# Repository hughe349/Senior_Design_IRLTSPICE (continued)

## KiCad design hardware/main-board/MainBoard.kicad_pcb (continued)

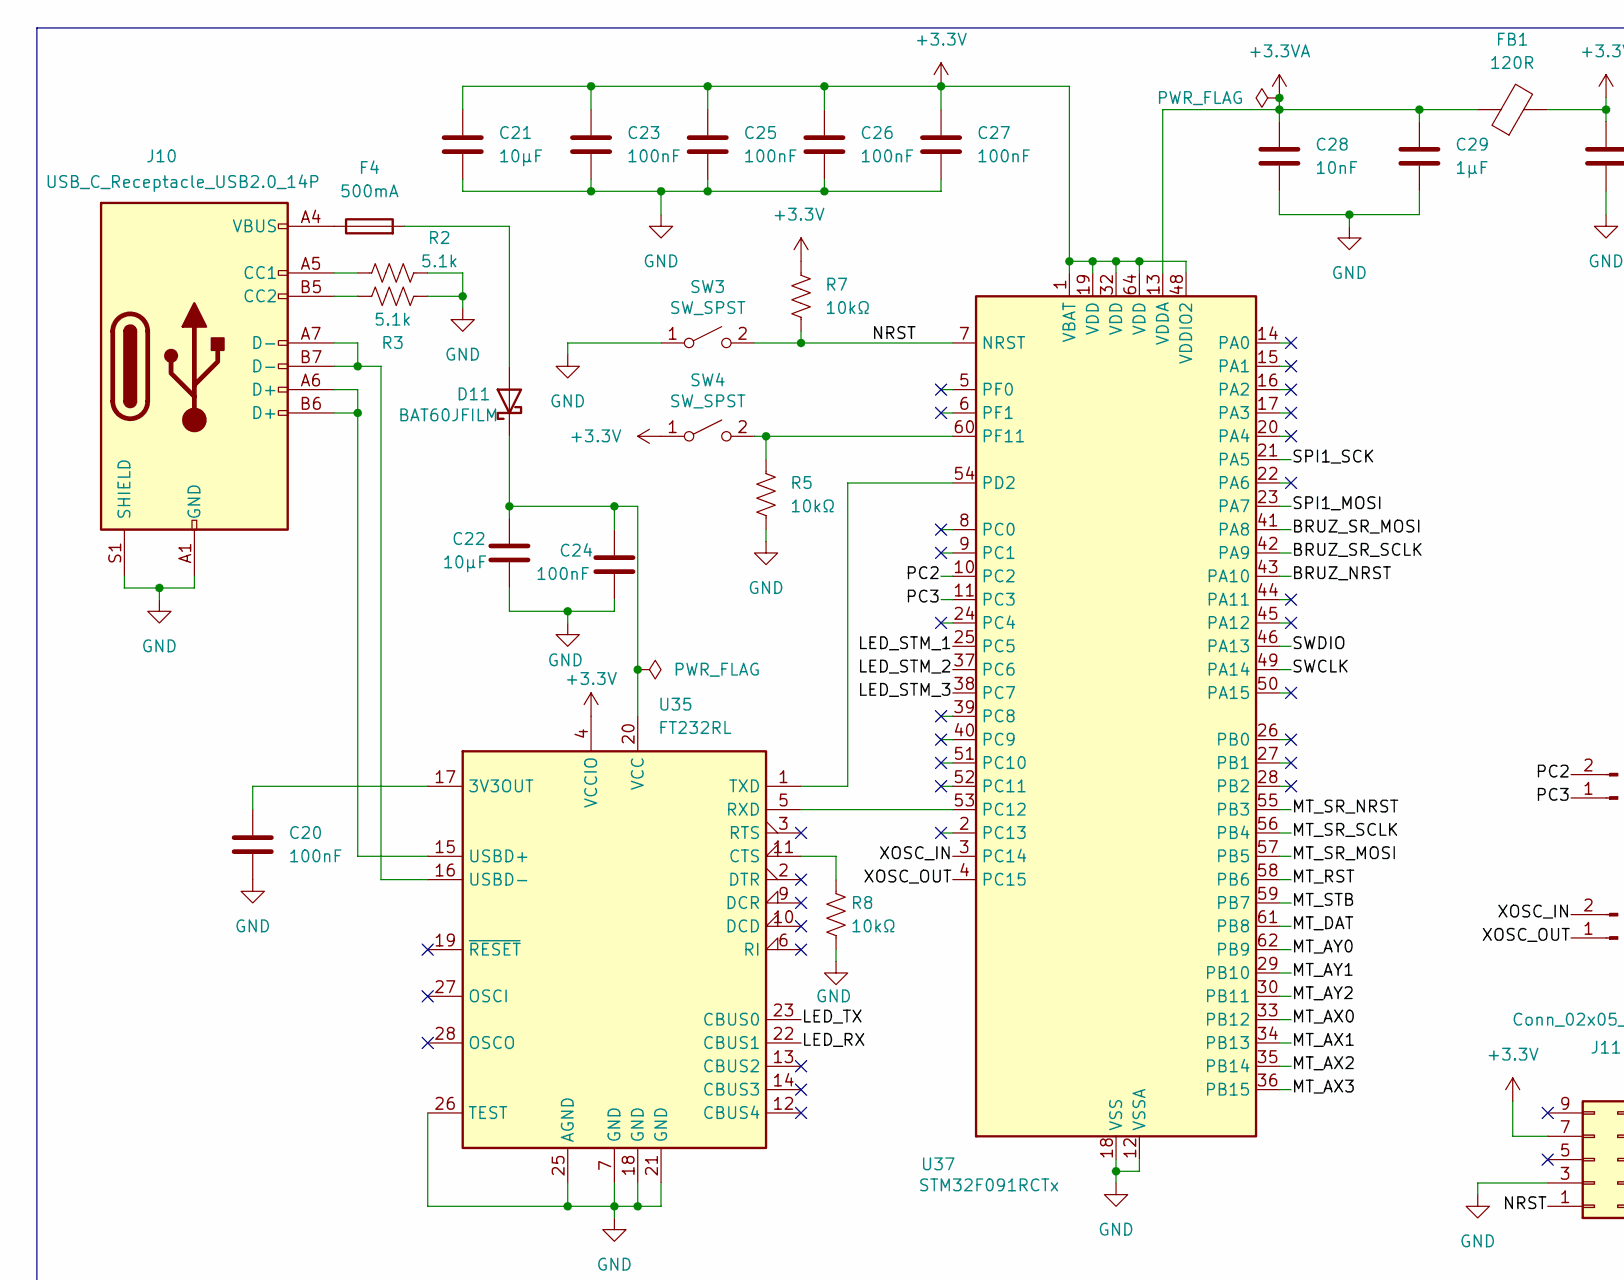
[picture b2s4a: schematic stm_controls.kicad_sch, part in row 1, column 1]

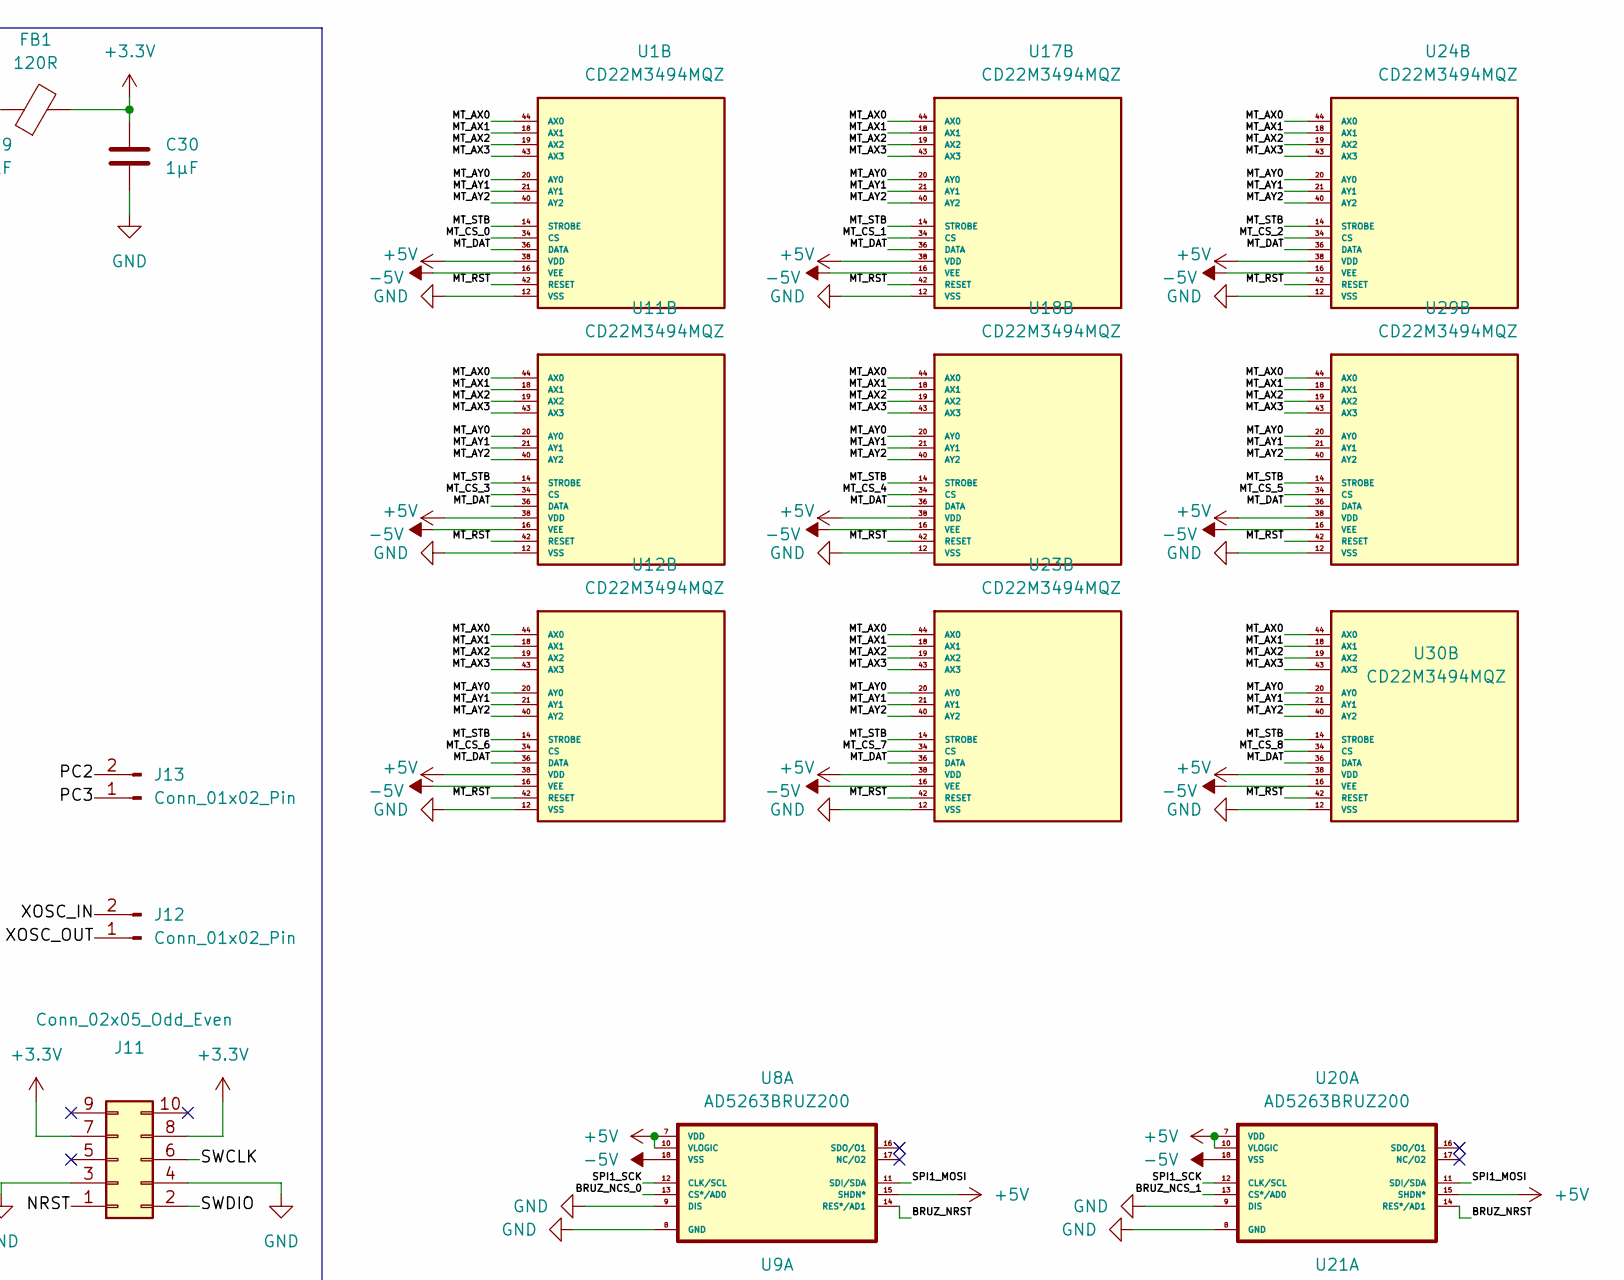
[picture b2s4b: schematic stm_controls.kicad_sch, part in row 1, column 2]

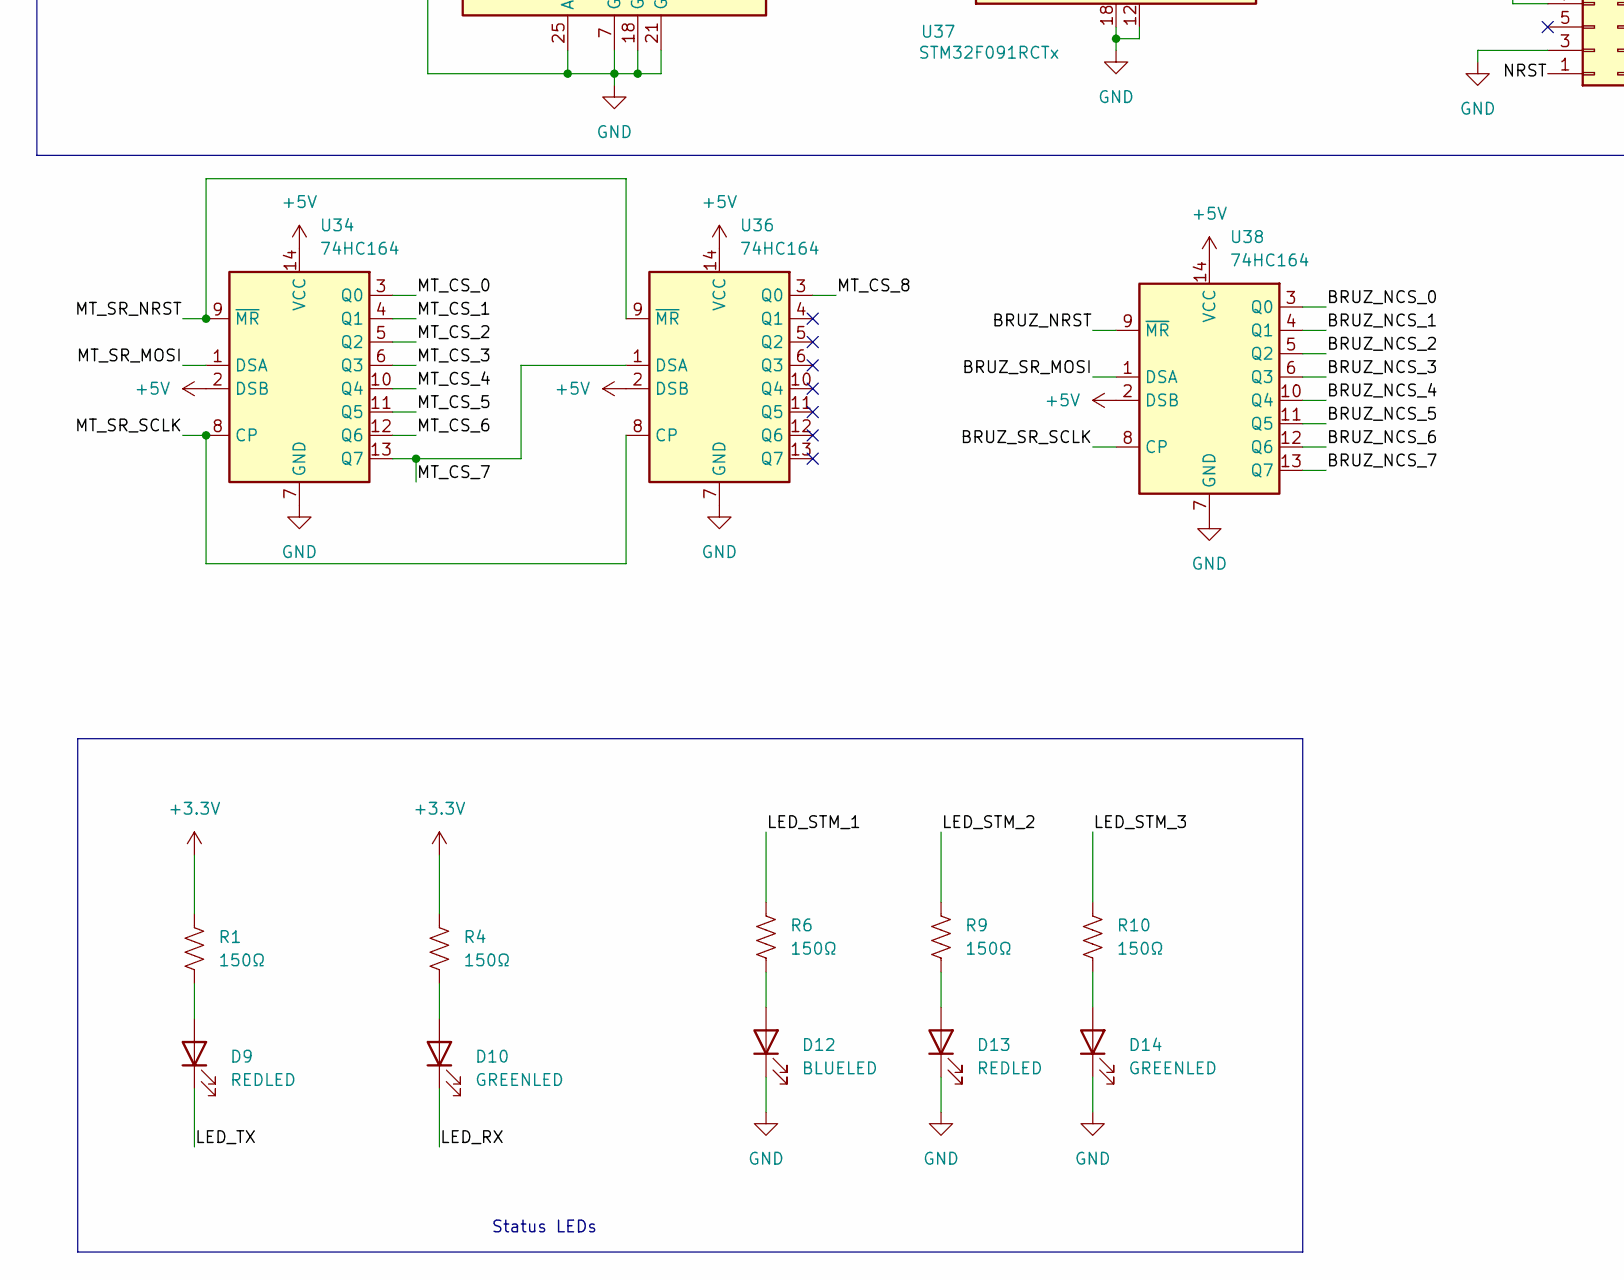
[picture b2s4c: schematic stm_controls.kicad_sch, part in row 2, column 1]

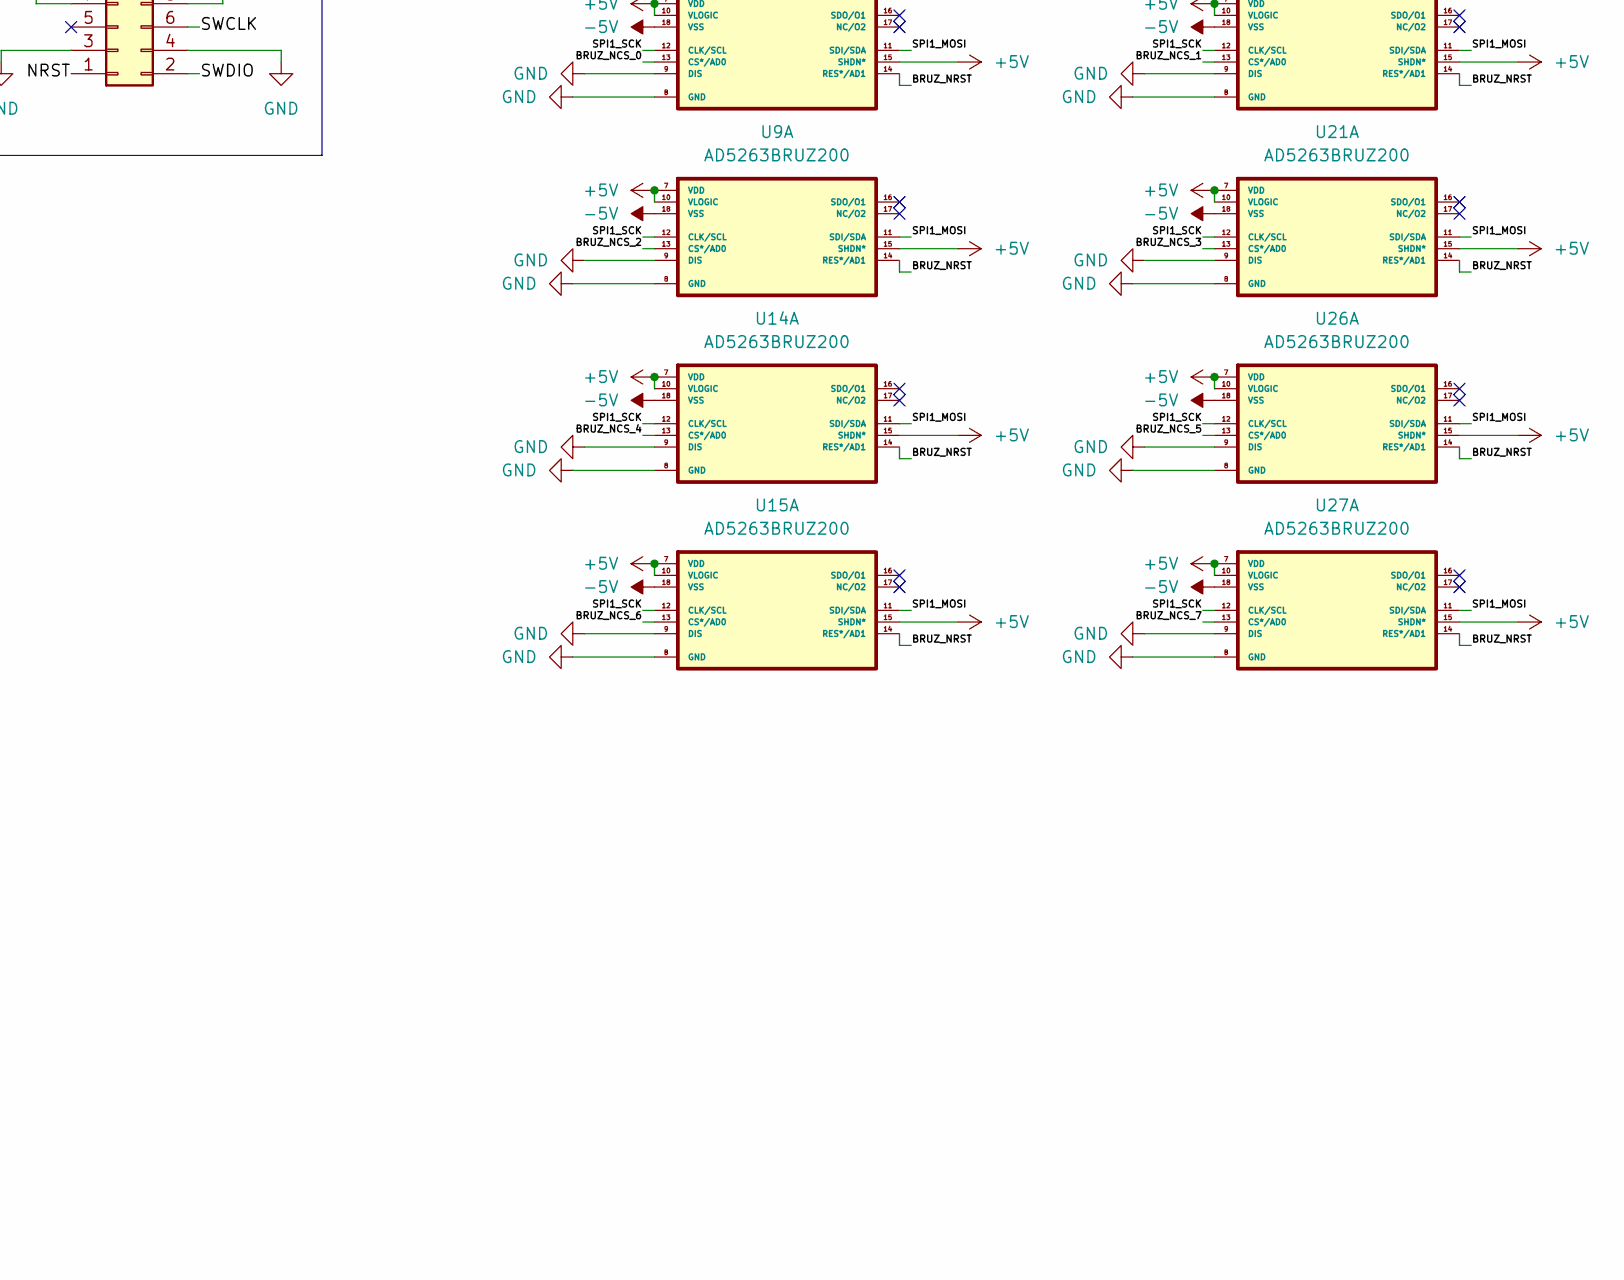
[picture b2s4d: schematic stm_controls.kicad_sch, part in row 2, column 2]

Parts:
C20, C23, C24, C25, C26, C27: 100nF; C_0603_1608Metric_Pad1.08x0.95mm_HandSolder
C21, C22: 10µF; C_0603_1608Metric_Pad1.08x0.95mm_HandSolder
C28: 10nF; C_0603_1608Metric_Pad1.08x0.95mm_HandSolder
C29, C30: 1µF; C_0603_1608Metric_Pad1.08x0.95mm_HandSolder
D9, D13: REDLED; D_0805_2012Metric_Pad1.15x1.40mm_HandSolder
D10, D14: GREENLED; D_0805_2012Metric_Pad1.15x1.40mm_HandSolder
D11: BAT60JFILM; D_SOD-323_HandSoldering
D12: BLUELED; D_0805_2012Metric_Pad1.15x1.40mm_HandSolder
F4: 500mA; Fuse_0603_1608Metric_Pad1.05x0.95mm_HandSolder
FB1: 120R; L_0603_1608Metric_Pad1.05x0.95mm_HandSolder
J10: USB_C_Receptacle_USB2.0_14P; USB_C_Receptacle_G-Switch_GT-USB-7010ASV
J11: Conn_02x05_Odd_Even; PinHeader_2x05_P2.54mm_Vertical
J12, J13: Conn_01x02_Pin; PinSocket_1x02_P2.54mm_Vertical
R1, R4, R6, R9, R10: 150Ω; R_0603_1608Metric_Pad0.98x0.95mm_HandSolder
R2, R3: 5.1k; R_0603_1608Metric_Pad0.98x0.95mm_HandSolder
R5, R7, R8: 10kΩ; R_0603_1608Metric_Pad0.98x0.95mm_HandSolder
SW3, SW4: SW_SPST; SW_SPST_SKQG_WithoutStem
U1, U11, U12, U17, U18, U23, U24, U29, U30: CD22M3494MQZ; PLCC44_16P66X16P66_INR-M; PARTREV September 2011
U8, U9, U14, U15, U20, U21, U26, U27: AD5263BRUZ200; SOP65P640X120-24N
U34, U36, U38: 74HC164; SOIC-14_3.9x8.7mm_P1.27mm
U35: FT232RL; SSOP-28_5.3x10.2mm_P0.65mm
U37: STM32F091RCTx; LQFP-64_10x10mm_P0.5mm

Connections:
+3.3V: C21.1, C23.1, C25.1, C26.1, C27.1, C30.1, FB1.2, J11.7, J11.8, R1.1, R4.1, R7.1, SW4.1 (A), U35.4 (VCCIO), U37.1 (VBAT), U37.19 (VDD), U37.32 (VDD), U37.48 (VDDIO2), U37.64 (VDD); also elsewhere on the board
+3.3VA: C28.1, C29.1, FB1.1, U37.13 (VDDA)
+5V: U1.38 (VDD), U8.7 (VDD), U8.10 (VLOGIC), U8.15 (SHDN*), U9.7 (VDD), U9.10 (VLOGIC), U9.15 (SHDN*), U11.38 (VDD), U12.38 (VDD), U14.7 (VDD), U14.10 (VLOGIC), U14.15 (SHDN*), U15.7 (VDD), U15.10 (VLOGIC), U15.15 (SHDN*), U17.38 (VDD), U18.38 (VDD), U20.7 (VDD), U20.10 (VLOGIC), U20.15 (SHDN*), U21.7 (VDD), U21.10 (VLOGIC), U21.15 (SHDN*), U23.38 (VDD), U24.38 (VDD), U26.7 (VDD), U26.10 (VLOGIC), U26.15 (SHDN*), U27.7 (VDD), U27.10 (VLOGIC), U27.15 (SHDN*), U29.38 (VDD), U30.38 (VDD), U34.2 (DSB), U34.14 (VCC), U36.2 (DSB), U36.14 (VCC), U38.2 (DSB), U38.14 (VCC); also elsewhere on the board
-5V: U1.16 (VEE), U8.18 (VSS), U9.18 (VSS), U11.16 (VEE), U12.16 (VEE), U14.18 (VSS), U15.18 (VSS), U17.16 (VEE), U18.16 (VEE), U20.18 (VSS), U21.18 (VSS), U23.16 (VEE), U24.16 (VEE), U26.18 (VSS), U27.18 (VSS), U29.16 (VEE), U30.16 (VEE); also elsewhere on the board
/Cell_1_Buff: U1.13 (Y6); also elsewhere on the board
/Cell_1_Out: U18.10 (Y7); also elsewhere on the board
/Cell_2_Buff: U1.10 (Y7); also elsewhere on the board
/MicroController/BRUZ_NCS_0: U8.13 (CS*/AD0), U38.3 (Q0)
/MicroController/BRUZ_NCS_1: U20.13 (CS*/AD0), U38.4 (Q1)
/MicroController/BRUZ_NCS_2: U9.13 (CS*/AD0), U38.5 (Q2)
/MicroController/BRUZ_NCS_3: U21.13 (CS*/AD0), U38.6 (Q3)
/MicroController/BRUZ_NCS_4: U14.13 (CS*/AD0), U38.10 (Q4)
/MicroController/BRUZ_NCS_5: U26.13 (CS*/AD0), U38.11 (Q5)
/MicroController/BRUZ_NCS_6: U15.13 (CS*/AD0), U38.12 (Q6)
/MicroController/BRUZ_NCS_7: U27.13 (CS*/AD0), U38.13 (Q7)
/MicroController/BRUZ_NRST: U8.14 (RES*/AD1), U9.14 (RES*/AD1), U14.14 (RES*/AD1), U15.14 (RES*/AD1), U20.14 (RES*/AD1), U21.14 (RES*/AD1), U26.14 (RES*/AD1), U27.14 (RES*/AD1), U37.43 (PA10), U38.9 (~MR)
/MicroController/BRUZ_SR_MOSI: U37.41 (PA8), U38.1 (DSA)
/MicroController/BRUZ_SR_SCLK: U37.42 (PA9), U38.8 (CP)
/MicroController/LED_RX: D10.1 (K), U35.22 (CBUS1)
/MicroController/LED_STM_1: R6.1, U37.25 (PC5)
/MicroController/LED_STM_2: R9.1, U37.37 (PC6)
/MicroController/LED_STM_3: R10.1, U37.38 (PC7)
/MicroController/LED_TX: D9.1 (K), U35.23 (CBUS0)
/MicroController/MT_AX0: U1.44 (AX0), U11.44 (AX0), U12.44 (AX0), U17.44 (AX0), U18.44 (AX0), U23.44 (AX0), U24.44 (AX0), U29.44 (AX0), U30.44 (AX0), U37.33 (PB12)
/MicroController/MT_AX1: U1.18 (AX1), U11.18 (AX1), U12.18 (AX1), U17.18 (AX1), U18.18 (AX1), U23.18 (AX1), U24.18 (AX1), U29.18 (AX1), U30.18 (AX1), U37.34 (PB13)
/MicroController/MT_AX2: U1.19 (AX2), U11.19 (AX2), U12.19 (AX2), U17.19 (AX2), U18.19 (AX2), U23.19 (AX2), U24.19 (AX2), U29.19 (AX2), U30.19 (AX2), U37.35 (PB14)
/MicroController/MT_AX3: U1.43 (AX3), U11.43 (AX3), U12.43 (AX3), U17.43 (AX3), U18.43 (AX3), U23.43 (AX3), U24.43 (AX3), U29.43 (AX3), U30.43 (AX3), U37.36 (PB15)
/MicroController/MT_AY0: U1.20 (AY0), U11.20 (AY0), U12.20 (AY0), U17.20 (AY0), U18.20 (AY0), U23.20 (AY0), U24.20 (AY0), U29.20 (AY0), U30.20 (AY0), U37.62 (PB9)
/MicroController/MT_AY1: U1.21 (AY1), U11.21 (AY1), U12.21 (AY1), U17.21 (AY1), U18.21 (AY1), U23.21 (AY1), U24.21 (AY1), U29.21 (AY1), U30.21 (AY1), U37.29 (PB10)
/MicroController/MT_AY2: U1.40 (AY2), U11.40 (AY2), U12.40 (AY2), U17.40 (AY2), U18.40 (AY2), U23.40 (AY2), U24.40 (AY2), U29.40 (AY2), U30.40 (AY2), U37.30 (PB11)
/MicroController/MT_CS_0: U1.34 (CS), U34.3 (Q0)
/MicroController/MT_CS_1: U17.34 (CS), U34.4 (Q1)
/MicroController/MT_CS_2: U24.34 (CS), U34.5 (Q2)
/MicroController/MT_CS_3: U11.34 (CS), U34.6 (Q3)
/MicroController/MT_CS_4: U18.34 (CS), U34.10 (Q4)
/MicroController/MT_CS_5: U29.34 (CS), U34.11 (Q5)
/MicroController/MT_CS_6: U12.34 (CS), U34.12 (Q6)
/MicroController/MT_CS_7: U23.34 (CS), U34.13 (Q7), U36.1 (DSA)
/MicroController/MT_CS_8: U30.34 (CS), U36.3 (Q0)
/MicroController/MT_DAT: U1.36 (DATA), U11.36 (DATA), U12.36 (DATA), U17.36 (DATA), U18.36 (DATA), U23.36 (DATA), U24.36 (DATA), U29.36 (DATA), U30.36 (DATA), U37.61 (PB8)
/MicroController/MT_RST: U1.42 (RESET), U11.42 (RESET), U12.42 (RESET), U17.42 (RESET), U18.42 (RESET), U23.42 (RESET), U24.42 (RESET), U29.42 (RESET), U30.42 (RESET), U37.58 (PB6)
/MicroController/MT_SR_MOSI: U34.1 (DSA), U37.57 (PB5)
/MicroController/MT_SR_NRST: U34.9 (~MR), U36.9 (~MR), U37.55 (PB3)
/MicroController/MT_SR_SCLK: U34.8 (CP), U36.8 (CP), U37.56 (PB4)
/MicroController/MT_STB: U1.14 (STROBE), U11.14 (STROBE), U12.14 (STROBE), U17.14 (STROBE), U18.14 (STROBE), U23.14 (STROBE), U24.14 (STROBE), U29.14 (STROBE), U30.14 (STROBE), U37.59 (PB7)
/MicroController/NRST: J11.1, R7.2, SW3.2 (B), U37.7 (NRST)
/MicroController/PC2: J13.2, U37.10 (PC2)
/MicroController/PC3: J13.1, U37.11 (PC3)
/MicroController/SPI1_MOSI: U8.11 (SDI/SDA), U9.11 (SDI/SDA), U14.11 (SDI/SDA), U15.11 (SDI/SDA), U20.11 (SDI/SDA), U21.11 (SDI/SDA), U26.11 (SDI/SDA), U27.11 (SDI/SDA), U37.23 (PA7)
/MicroController/SPI1_SCK: U8.12 (CLK/SCL), U9.12 (CLK/SCL), U14.12 (CLK/SCL), U15.12 (CLK/SCL), U20.12 (CLK/SCL), U21.12 (CLK/SCL), U26.12 (CLK/SCL), U27.12 (CLK/SCL), U37.21 (PA5)
/MicroController/SWCLK: J11.6, U37.49 (PA14)
/MicroController/SWDIO: J11.2, U37.46 (PA13)
/MicroController/XOSC_IN: J12.2, U37.3 (PC14)
/MicroController/XOSC_OUT: J12.1, U37.4 (PC15)
/STD1/C3_in: U17.8 (X10); also elsewhere on the board
/STD1/C3_out: U17.9 (X11); also elsewhere on the board
/STD1/C4_out: U17.7 (X9); also elsewhere on the board
/STD1/R2_out: U18.7 (X9); also elsewhere on the board
/STD1/R4_in: U18.8 (X10); also elsewhere on the board
/STD1/R4_out: U18.9 (X11); also elsewhere on the board
/STD1/Y5: U17.15 (Y5); also elsewhere on the board
/STD1/Y6: U17.13 (Y6); also elsewhere on the board
/STD1/Y7: U17.10 (Y7); also elsewhere on the board
/STD1_Y0: U18.17 (Y4); also elsewhere on the board
/STD1_Y1: U18.15 (Y5); also elsewhere on the board
/STD1_Y2: U18.13 (Y6); also elsewhere on the board
/STD2_Y0: U1.2 (X14); also elsewhere on the board
/STD2_Y1: U1.3 (X15); also elsewhere on the board
/STD2_Y2: U1.4 (X6); also elsewhere on the board
/STD3/Y0: U1.5 (X7); also elsewhere on the board
/STD3/Y1: U1.6 (X8); also elsewhere on the board
/STD3/Y2: U1.7 (X9); also elsewhere on the board
/STD_Out: U1.8 (X10); also elsewhere on the board
GND: C20.2, C21.2, C22.2, C23.2, C24.2, C25.2, C26.2, C27.2, C28.2, C29.2, C30.2, D12.1 (K), D13.1 (K), D14.1 (K), J10.A1 (GND), J10.A12 (GND), J10.B1 (GND), J10.B12 (GND), J10.S1 (SHIELD), J11.3, J11.4, R2.2, R3.2, R5.2, R8.2, SW3.1 (A), U1.12 (VSS), U8.8 (GND), U8.9 (DIS), U9.8 (GND), U9.9 (DIS), U11.12 (VSS), U12.12 (VSS), U14.8 (GND), U14.9 (DIS), U15.8 (GND), U15.9 (DIS), U17.12 (VSS), U17.17 (Y4), U18.12 (VSS), U20.8 (GND), U20.9 (DIS), U21.8 (GND), U21.9 (DIS), U23.12 (VSS), U24.12 (VSS), U26.8 (GND), U26.9 (DIS), U27.8 (GND), U27.9 (DIS), U29.12 (VSS), U30.12 (VSS), U34.7 (GND), U35.7 (GND), U35.18 (GND), U35.21 (GND), U35.25 (AGND), U35.26 (TEST), U36.7 (GND), U37.12 (VSSA), U37.18 (VSS), U37.31 (VSS), U37.47 (VSS), U37.63 (VSS), U38.7 (GND); also elsewhere on the board
unnamed: D9.2 (A), R1.2
unnamed: D10.2 (A), R4.2
unnamed: D11.2 (A), F4.2
unnamed: C22.1, C24.1, D11.1 (K), U35.20 (VCC)
unnamed: D12.2 (A), R6.2
unnamed: D13.2 (A), R9.2
unnamed: D14.2 (A), R10.2
unnamed: F4.1, J10.A4 (VBUS), J10.A9 (VBUS), J10.B4 (VBUS), J10.B9 (VBUS)
unnamed: J10.A5 (CC1), R2.1
unnamed: J10.B5 (CC2), R3.1
unnamed: R5.1, SW4.2 (B), U37.60 (PF11)
unnamed: C20.1, U35.17 (3V3OUT)
unnamed: R8.1, U35.11 (CTS)
unnamed: U35.5 (RXD), U37.53 (PC12)
unnamed: U35.1 (TXD), U37.54 (PD2)
unnamed: J10.A6 (D+), J10.B6 (D+), U35.15 (USBD+)
unnamed: J10.A7 (D-), J10.B7 (D-), U35.16 (USBD-)

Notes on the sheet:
Status LEDs

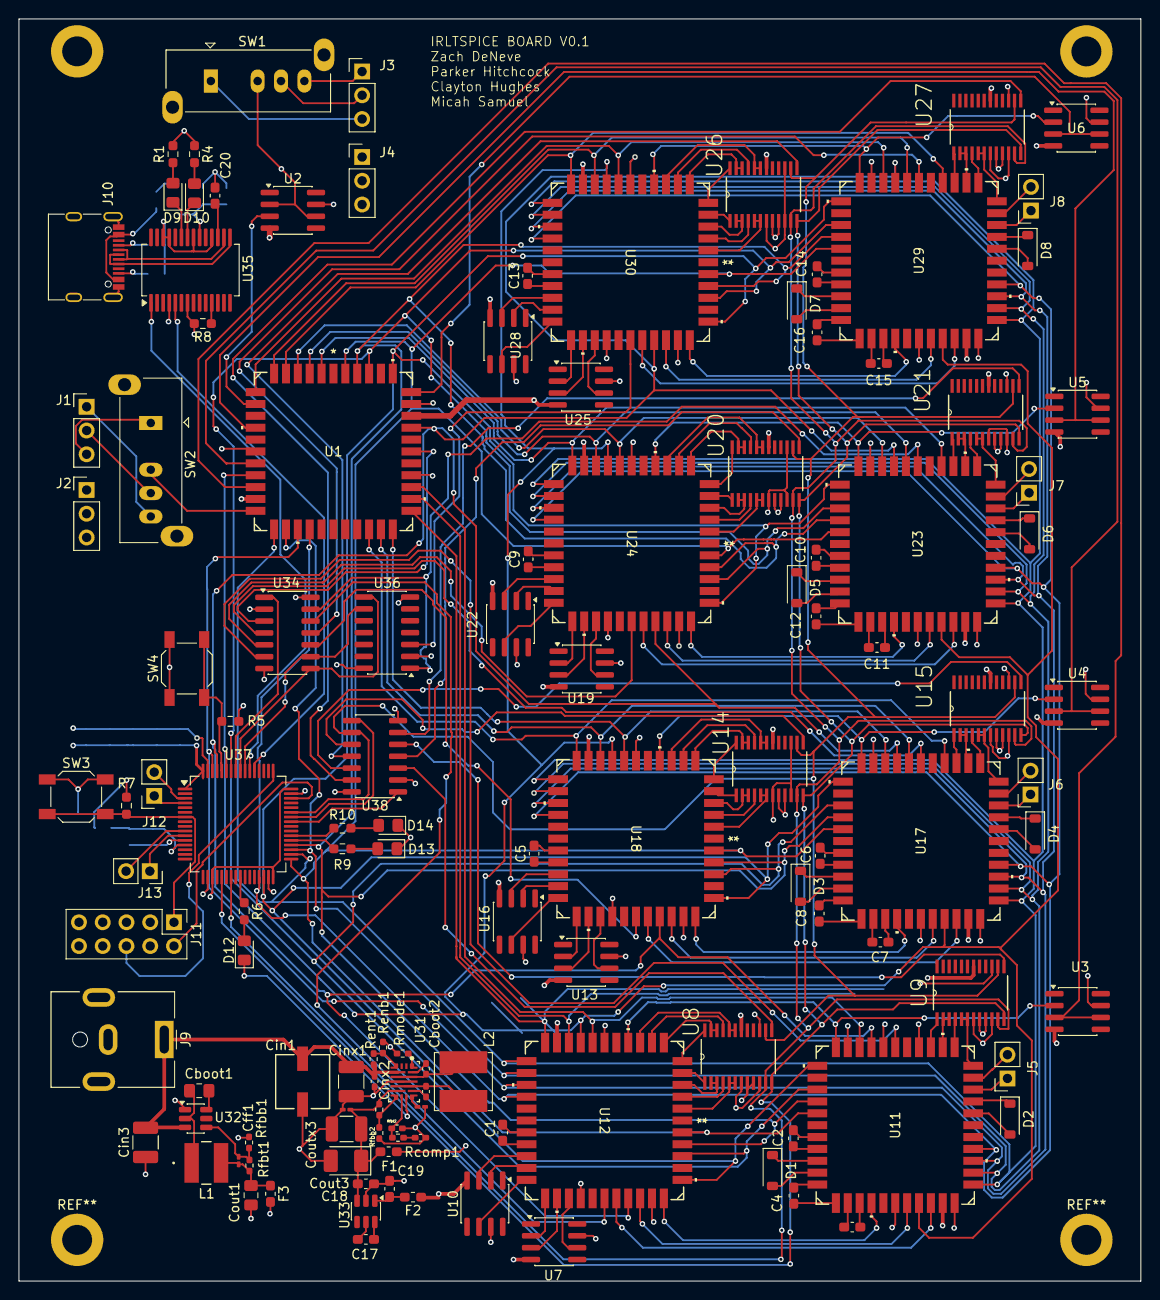
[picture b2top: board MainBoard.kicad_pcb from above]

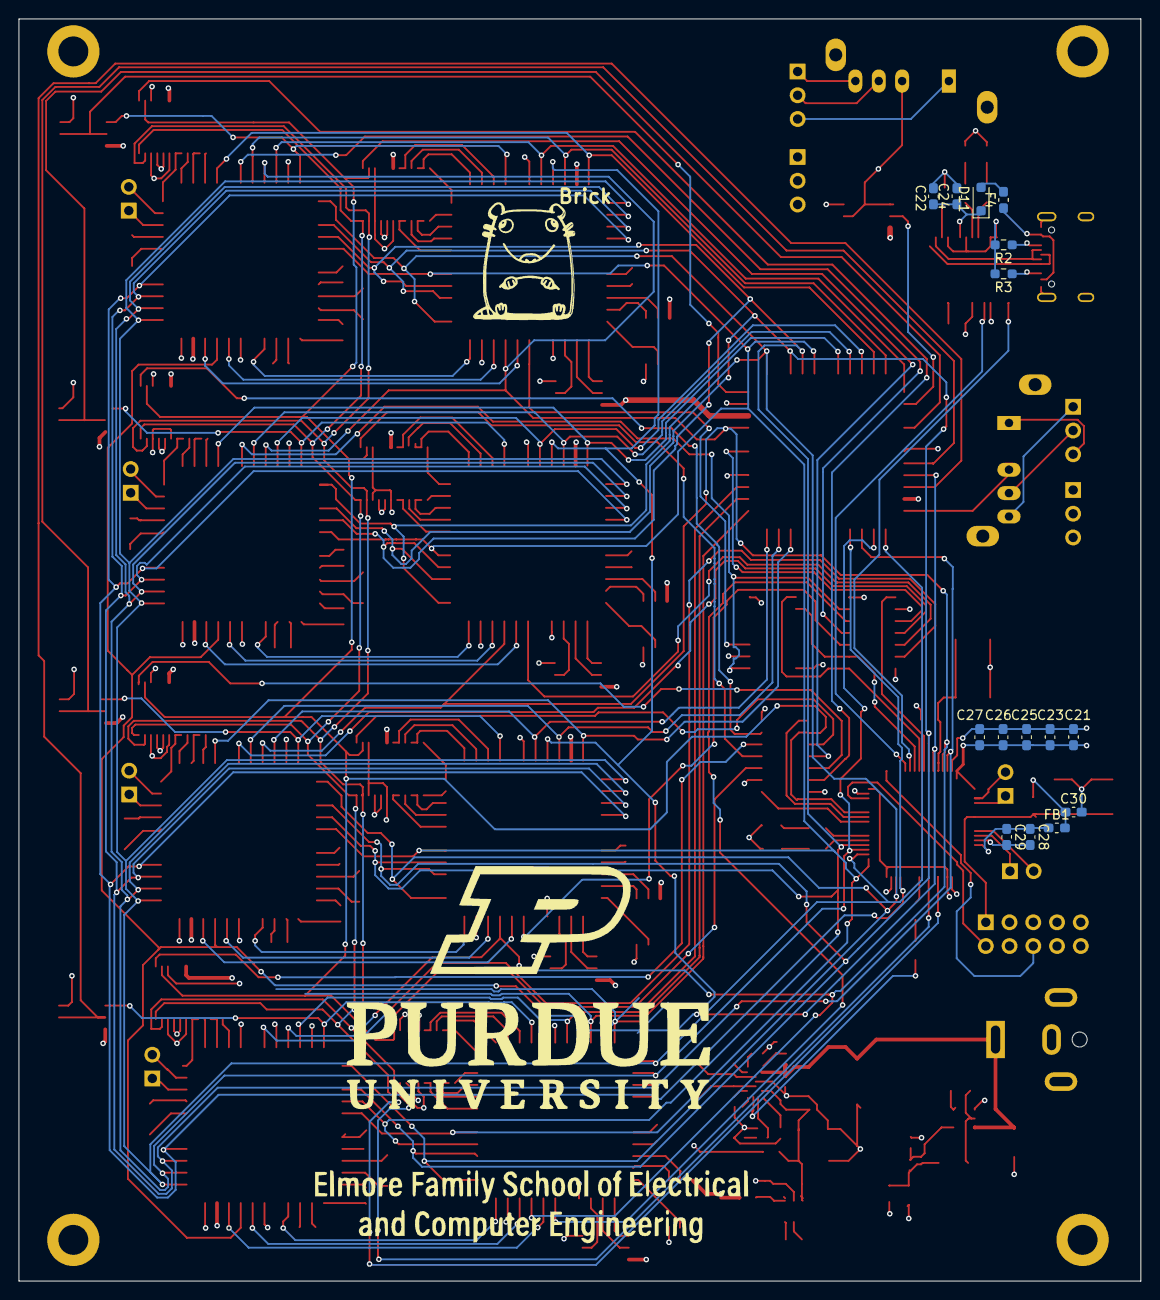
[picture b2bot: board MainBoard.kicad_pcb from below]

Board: 4 copper layers, 120.0 x 135.0 mm, 140 parts (16 on the bottom side), 257 nets.

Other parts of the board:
Brick: LOGO

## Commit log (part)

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2026-01-23 setup
2026-01-23 version: Upgrade to KiCad 9
2026-01-23 Added Crossbar and symbol library
2026-01-23 organization: Migrate to hardware dir
2026-01-28 stuff
2026-01-28 feat: top level schem
2026-01-28 fix: top level sectioning
2026-01-28 feat: added power amp to top
2026-01-28 feat: Software initial commit
2026-01-28 feat: Add boost dep + testing
2026-01-30 feat: Formatting + netlist beginnings
2026-02-06 Changed cell design added new resistors
2026-02-11 Power Supply schematic added and power amp design changed. Initial Design stage.
2026-02-11 Clayton's fun routing fix
2026-02-11 feat: Parser class setup
2026-02-18 feat: Tokenizing of spice file
2026-02-18 feat: Line grouping
2026-02-20 feat: Netlist graph for resistors and caps
2026-02-20 feat: base firmware drivers
2026-02-25 feat: Parameterized component parsing
2026-02-27 Added Digital Pot Symbol and created Senior Design Footprint Library
2026-03-04 reafactor: Parsers just make netlists
2026-03-04 added symbol and footprint for new crossbar MT8816
2026-03-04 feat: Awesome compiler options
2026-03-04 symbol update
2026-03-04 small change
2026-03-04 small change 2
2026-03-04 feat: stm32 IC controls
2026-03-04 Big Changes in the Schematic World
2026-03-04 feat: Verificaiton engine
2026-03-04 feat: Unconnected pruning + listS refactor
2026-03-06 God is Real, God is Real, Im not kidding this time I wouldn't joke about this
2026-03-06 feat: reworked drivers
2026-03-06 feat: Models + some rules
2026-03-06 Added TPS55285 Foot and Sym
2026-03-06 feat: Assgnment + show-nets flag
2026-03-06 fortnite info cache
2026-03-06 We are nuking the fp-info-cache
2026-03-08 chore: Delete fp-info-cache
2026-03-08 Updated Footprints and Controls
2026-03-08 Designated majority of footprints
2026-03-09 Fully filled footprints
2026-03-09 feat: Graph rules + assignment data structure
2026-03-10 PCB comps in, and formatted
2026-03-11 feat: Cell assignment maybe working
2026-03-11 feat: Verbose flags + cleanup
2026-03-11 designed Power PCB section layout
2026-03-12 small edits with layout discussion
2026-03-13 feat: drivers for demo
2026-03-13 Working on that PCP
2026-03-13 The PCB is coming together
2026-03-15 Added wiring to cells and compacted input
2026-03-15 added some intercell connections
2026-03-16 Squishing Standard Cells Together
2026-03-16 started cross board traces for data and signal in bot cell
2026-03-16 Standard cell 1 finalizations
2026-03-17 linked outside AX and AY and other controls
2026-03-18 STD2 Analog
2026-03-18 ran more control lines on cell 0 and 1
2026-03-19 Standard cell 2
2026-03-19 feat: Board Info + wip on custom
2026-03-19 completed AX and AY on all cells, started ground and power plane
2026-03-20 Almost done with the control
2026-03-20 I Love You Big Sean
2026-03-21 created power plane, tweeked track sizes
2026-03-21 I think Parker would look good if he got shot in the head
2026-03-22 finalized input output and power plane
2026-03-22 feat: Schematic changes for top level +/-5V
2026-03-22 feat: Routing for top level +/- 5V
2026-03-23 fix: New std cells
2026-03-23 ci: Precommit config I've secretly been using
2026-03-23 feat: wip on connection making
2026-03-23 added ground conn and fixed switches
2026-03-23 feat: ERC + DRC fixes
2026-03-23 feat: Diodes bigger
2026-03-23 added drc rules for JLC
2026-03-23 feat: Part nos plus some micro fixup
2026-03-24 finalized component list, fixed DRC errors
2026-03-24 Top 10 Minecraft Youtubers who have sworn
2026-03-24 part numbers
2026-03-25 feat: uart byte header
2026-03-25 feat: top-level routing done
2026-03-25 feat: Number overhaul
2026-03-26 feat: Better numbers
2026-03-27 feat: Simple component connections done
2026-03-27 feat: renaming chips
2026-03-27 Little Backup PCB Addition
2026-03-27 fix: Cap allocaion values + opamp pin
2026-03-27 feat: Resistor quantization
2026-03-28 started single cell pcb
2026-03-30 Updated scheme on backup
2026-04-01 feat: reset config added
2026-04-01 feat: WIP on board programmer
2026-04-01 feat: reset response/enum added
2026-04-01 feat: Basic serial being sent
2026-04-01 build: Boost to .tar.xz for download time
2026-04-03 feat: adding sr drivers
2026-04-03 feat: prelim testing
2026-04-03 feat: prefix/message testing
2026-04-03 feat: remove manual testing code
2026-04-03 fix: Better defaults
2026-04-03 feat: renaming states
2026-04-03 feat: com protocol
2026-04-03 feat: reset pots added
2026-04-03 feat: Programming done-ish
2026-04-03 feat: return to config ack
2026-04-03 feat: swap x and y pos
2026-04-03 feat: Programming minimum viable product!
2026-04-03 feat: todo comment
2026-04-03 feat: fix dump
2026-04-03 fix: debug enabling
2026-04-08 feat: redo clock config
2026-04-08 feat: redo sr drivers
2026-04-08 chore: deadcode
2026-04-08 feat: sr enum
2026-04-08 fix: remove to_array
2026-04-08 ci: Fix Linux + Mac builds
2026-04-08 build: Some compatibility stuff
2026-04-08 ci: GH actions attempt 1
2026-04-08 fix: Leaking parsers
2026-04-08 fix: flagify uses std::array
2026-04-08 fix: VLAs aren't in c++
2026-04-08 ci: GH actions attempt 3
2026-04-08 ci: GH actions MSVC .exe
2026-04-08 fix: size_t literals
2026-04-08 fix: MSVC for real maybe
2026-04-08 build: Constexpr and renames to make msvc happy
2026-04-08 feat: Mock programming + flag fix
2026-04-08 fix: Chainedcrossbar vectors for msvc
2026-04-08 fix: Initializer + git rid of "Testing"
2026-04-08 fix: MSVC please?!?!
2026-04-08 clean: Make rule an existence check
2026-04-08 ci: GH actions attempt 2
2026-04-08 ci: GH actions MSVC build dir
2026-04-08 ci: GH actions attempt 5
2026-04-08 ci: GH actions attempt 6
2026-04-08 ci: GH actions attempt 4
2026-04-13 feat: updating drivers
2026-04-13 feat: update for pcb testing
2026-04-13 fix: function definition clarity
2026-04-19 AAAAAAAAH
2026-04-19 format: Boost includes to system
2026-04-19 feat: Begin crossbar fixer
2026-04-20 I ate the fillet 'o fish
2026-04-21 ci: CMake uses CPM + ccache for speedup
2026-04-21 fix: Cross platform home dir
2026-04-21 fix: Cross platform home dir attempt 2
2026-04-21 docs: Update README
2026-04-22 Parker Loves Furries
2026-04-24 feat: Timing worst case
2026-04-24 I know of at least one
2026-04-27 feat: WIP on manufacturability
2026-04-28 PCB done
2026-04-29 feat: Optimize crossbar data transmission
2026-04-30 wip: Whatever Micah had before I touched him
2026-04-30 feat: Working on breadboard
2026-04-30 feat: xpin/ypin addressing for function
2026-04-30 feat: single cell implementation
2026-04-30 feat: refactor single cell code
2026-04-30 feat: simpler bruz drivers
2026-04-30 fix: bruz drivers
2026-04-30 feat: bruz latch enable fix
2026-04-30 feat: Minimal main
2026-04-30 feat: bruz drivers
2026-04-30 feat: programming real board
2026-04-30 fix: bruz indexing
2026-04-30 feat: 0 resistance prevention
2026-05-01 feat: Demos + evil bruzz removal
2026-05-01 fix: Bruz addressing
2026-05-01 cleanup: Main bs
2026-05-01 feat: state color matching
2026-05-01 feat: pot lowest res allowance
2026-05-01 feat: Some 2 cell stuff
2026-05-02 feat: Evil opamp rule + some demos
2026-05-04 chore: Add LICENSE
